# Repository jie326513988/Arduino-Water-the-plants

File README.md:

## 一款迷你型的植物浇水系统，包括代码、电路板原理图PCB图和适用3D打印的外壳

.jpg)
#### 注意！所有版本PCB未加到电池低压保护，电池过放会导致电池寿命下降，请使用带保护板的电池，不要让电池电压低于3.0V。
#### 2021-4-11 v1.1.4c版本发布
* 1.修正休眠时间单位显示错误问题
* 2.修改字库位置为本地调用并去除用不上的符号字母
* 3.设置界面添加页码条动画
* 4.美化开机和唤醒检查土湿&电压的检查动画
#### 2021-1-17 LDO版本已验证成功，适合3D打印的外壳已测试成功
## 特点
* 根据自己设定的土壤湿度阈值进行浇水，而不是简单定时浇水，避免不必要的浇水。
* 无浇水任务时自动进入休眠以节省电量，休眠电流0.6ma，满足数周充一次电（小型花盆），配合太阳能充电器可实现长期无人监管。
* MX612E电机驱动芯片，支持pwm调节水泵速度，带过热断电保护。
* 主控PCB+电容式土壤湿度检测PCB的组合结构，主控集成土湿驱动电路，传感器可飞线，也可将从侧面焊接到主控板上，实现更高的集成度。
* 观看视频 https://www.bilibili.com/video/BV1UV411b7vG

## 使用说明（必看）
* 按键1：确认/唤醒，按键2：上/加/左，按键3：下/减/右，按下下键不放再按下确认键即可软重启系统
* 主界面可切换 AUTO/OFF 模式，AUTO模式手动浇水不可用、可自动休眠和唤醒，OFF模式可手动浇水、不会自动休眠和唤醒
* 主控板没有电池低压保护电路，电池过放会导致电池寿命下降，请使用带保护板的电池，不要让电池电压低于3.0V
* 初次使用建议校准参考电压，这样电量显示比较准。测量屏幕的供电电压就是参考电压
* 使用低放电倍率的电池可能会导致水泵启动时触发电池保护板的过流保护而断电，打开水泵平滑启动功能可改善这一现象，原因是有些水泵的启动电流太高导致触发保护，平滑启动可降低水泵的启动电流
* 使用6V蠕动泵，管径越大出水量越多，建议5mm的外径，3mm内径的硅胶管
* 出水口不能离土壤湿度传感器太远，太远湿度传递慢会导致花盆满水溢出
* 浇水速度不能太快，调节PWM MAX即可调节浇水速度，太快会导致只有传感器附近的土是湿的
* 想追求完美的浇水效果的话，需要将土壤湿度传感器水平埋在花盆底部，做好传感器的防水措施就行
* 使用4个M2x12螺丝固定面壳
## 菜单设置说明
* 土壤湿度菜单：设置浇水的上限和下限，启动浇水的延迟时间，停止浇水的延迟时间
* 水泵菜单：设置水泵超时时间（湿度增长率小于4%且持续设定的时间则自动停机休眠），设置水泵是否需要平滑启动，平滑启动的初始PWM值和PWM增量值
* 休眠&亮度菜单：设置休眠时间、亮屏时间、OLED亮度
* 电压&频率菜单：设置电池低压报警值、参考电压值、PWM频率、PWM最大值
* 土湿校准菜单：设置校准土壤湿度的范围，建议暴露在空气中校准为10%，浸泡在水中为95%
* 恢复出厂设置：重置所有参数

## 硬件配置
* 使用500mah，3.7V锂电池供电，休眠耗电0.6ma
* 外接OLED II2模块
* 带充电、升压、LDO电路
* 电机驱动电路
* 带电容式土壤湿度传感器驱动电路   

## 烧录说明
    1.将我提供的库文件放好位置
    2.方法a：使用空芯片，再用AVR ICSP在线烧录器或离线烧录器烧录引导或带引导的固件，之后使用CH340串口模块即可更新程序
      方法b：买一块UNO，上传好程序，将芯片拆下来再焊到浇水板子上
      方法c：使用Arduino uno作为icsp烧录器对空芯片进行烧录引导，再通过CH340上传程序
    3.使用ch340模块更新程序，需要手动复位，打开Arduino IDE，文件-首选项-显示详情输出-上传勾选，点击主界面上传按钮，看到下方出现Overriding Baud Rate: 115200，迅速按下复位按钮即可更新程序
.png)
.png)
.jpg)
.jpg)
.jpg)
.jpg)
.jpg)

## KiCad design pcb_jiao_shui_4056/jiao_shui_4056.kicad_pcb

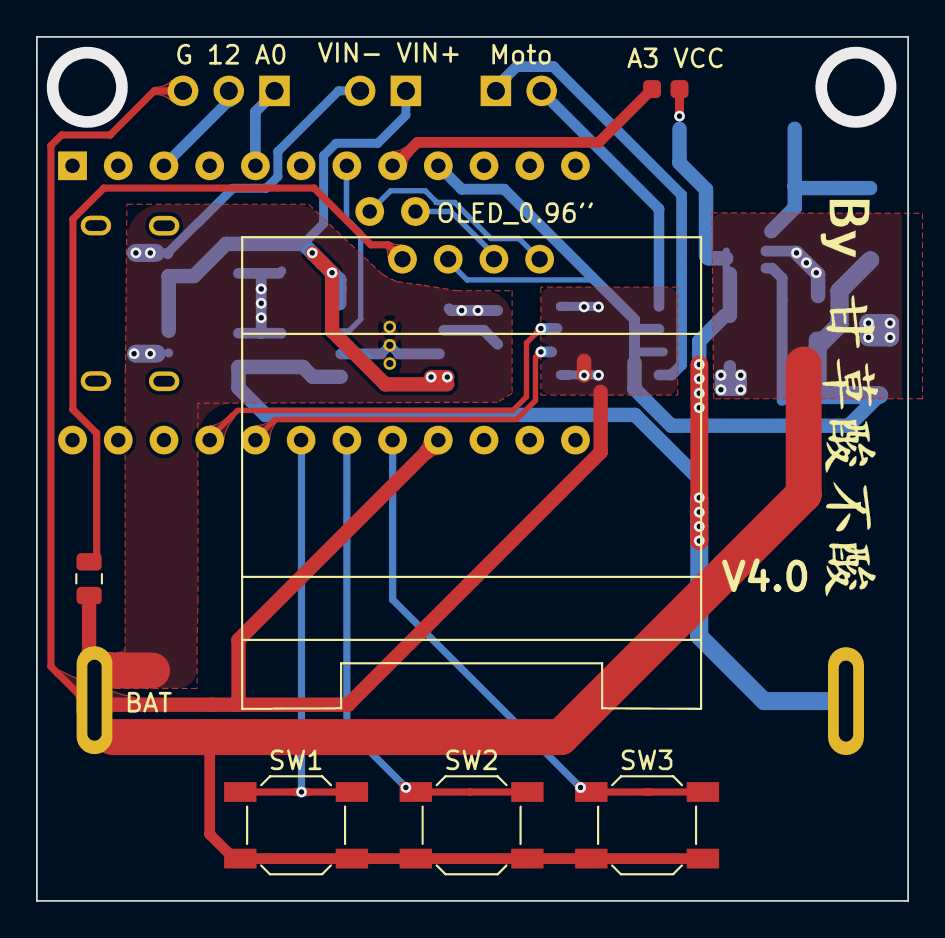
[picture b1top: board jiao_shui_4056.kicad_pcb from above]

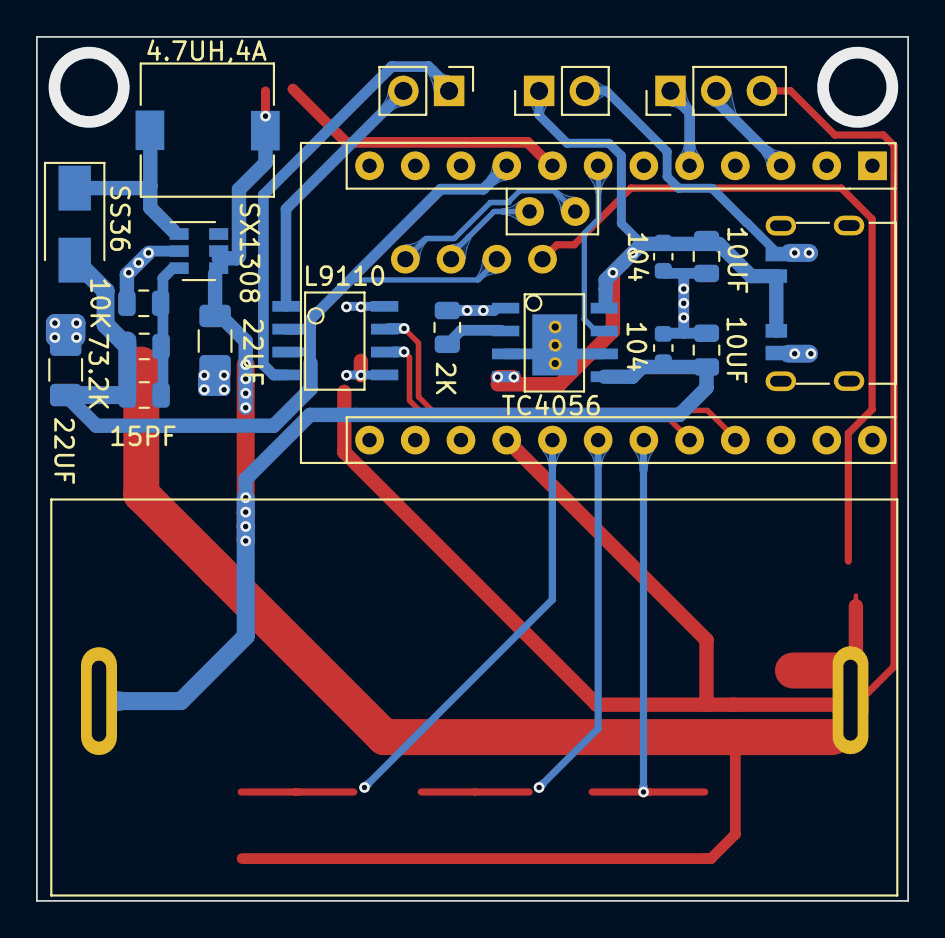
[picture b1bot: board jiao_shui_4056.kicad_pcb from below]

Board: 2 copper layers, 48.4 x 48.0 mm, 26 parts (21 on the bottom side), 20 nets.

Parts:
A1: Arduino_Pro_Mini_v1.0; Arduino_Pro_Mini_v1.0_lite
A2: OLED_0.96''; OLED_0.96''_25.5X26.2
C1, C3: 10UF; C_0805_2012Metric
C2, C4: 104; C_0603_1608Metric
C5, C7: 22UF; C_1206_3216Metric
C6: 15PF; C_0805_2012Metric
D1: SS36; D_SMA
J1: BAT; Batter_Box_16340
J2: Moto; PinHeader_1x02_P2.54mm_Vertical
J3: A3 VCC; 2p_duan_jie
J4: G 12 A0; PinHeader_1x03_P2.54mm_Vertical
J5: VIN- VIN+; PinHeader_1x02_P2.54mm_Vertical
L1: 4.7UH,4A; CDRH74R
L2: L9110; SOP-8
P1: USB_C_Plug_USB2.0; Type_C_Power
R2: 2K; R_0805_2012Metric
R3: 10K; R_0805_2012Metric
R4: 73.2K; R_0805_2012Metric
SW1, SW2, SW3: SW_SPST; SW_SPST_SKQG_WithStem
U1: TC4056; SOP-8-SR
U2: SX1308; SOT-23-6

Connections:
2: A1.5, SW3.1
3: A1.6, SW2.1
4: A1.7, SW1.1
5V: A1.27, A2.2, C6.2, C7.1, D1.2, L2.2, L2.3, R4.1
12: A1.15, J4.2
A0: A1.19, J4.1
A2: A1.21, U1.7
A3: A1.22, J3.2
A4: A1.23, A2.4
A5: A1.24, A2.3
BAT+: C3.1, C4.1, C5.1, J1.2, J3.1, L1.1, U1.5, U2.4, U2.5
GND: A1.4, A2.1, C1.2, C2.2, C3.2, C4.2, C5.2, C7.2, J1.1, J4.3, J5.2, L2.5, L2.8, P1.A1, P1.A12, P1.B1, P1.B12, R2.2, R3.1, SW1.2, SW2.2, SW3.2, U1.1, U1.3, U1.6, U2.2
unnamed: A1.8, L2.6
unnamed: A1.9, L2.7
unnamed: C6.1, R3.2, R4.2, U2.3
unnamed: D1.1, L1.2, U2.1
unnamed: J2.1, L2.4
unnamed: J2.2, L2.1
unnamed: R2.1, U1.2
VIN=5V: C1.1, C2.1, J5.1, P1.A4, P1.A9, P1.B4, P1.B9, U1.4, U1.8

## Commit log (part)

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2020-03-11 更新SS36二极管图片
    之前的二极管图片都显示反了，按图放置的话会烧掉SX1306升压芯片
2020-03-13 更新新的版本5.1
    二极管丝印图片修正，5.1版本添加47UF的电解电容，降低电机启动造成的供电不足。
